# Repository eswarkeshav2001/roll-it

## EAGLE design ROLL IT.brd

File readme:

Guys,Here i have add all the necessary files
PCB credits:Manikandan paramasivam

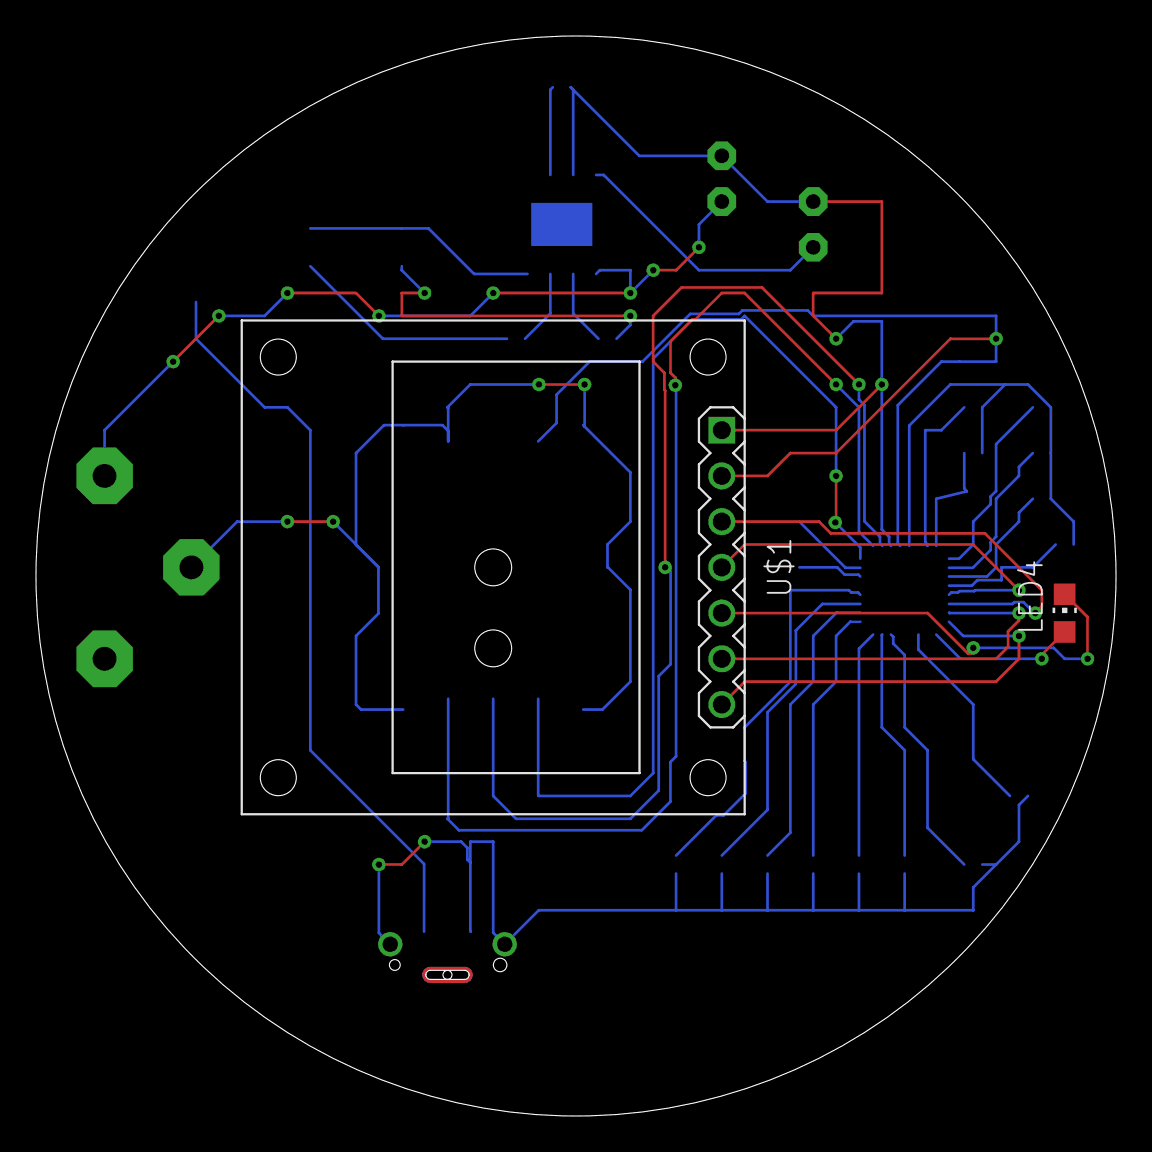
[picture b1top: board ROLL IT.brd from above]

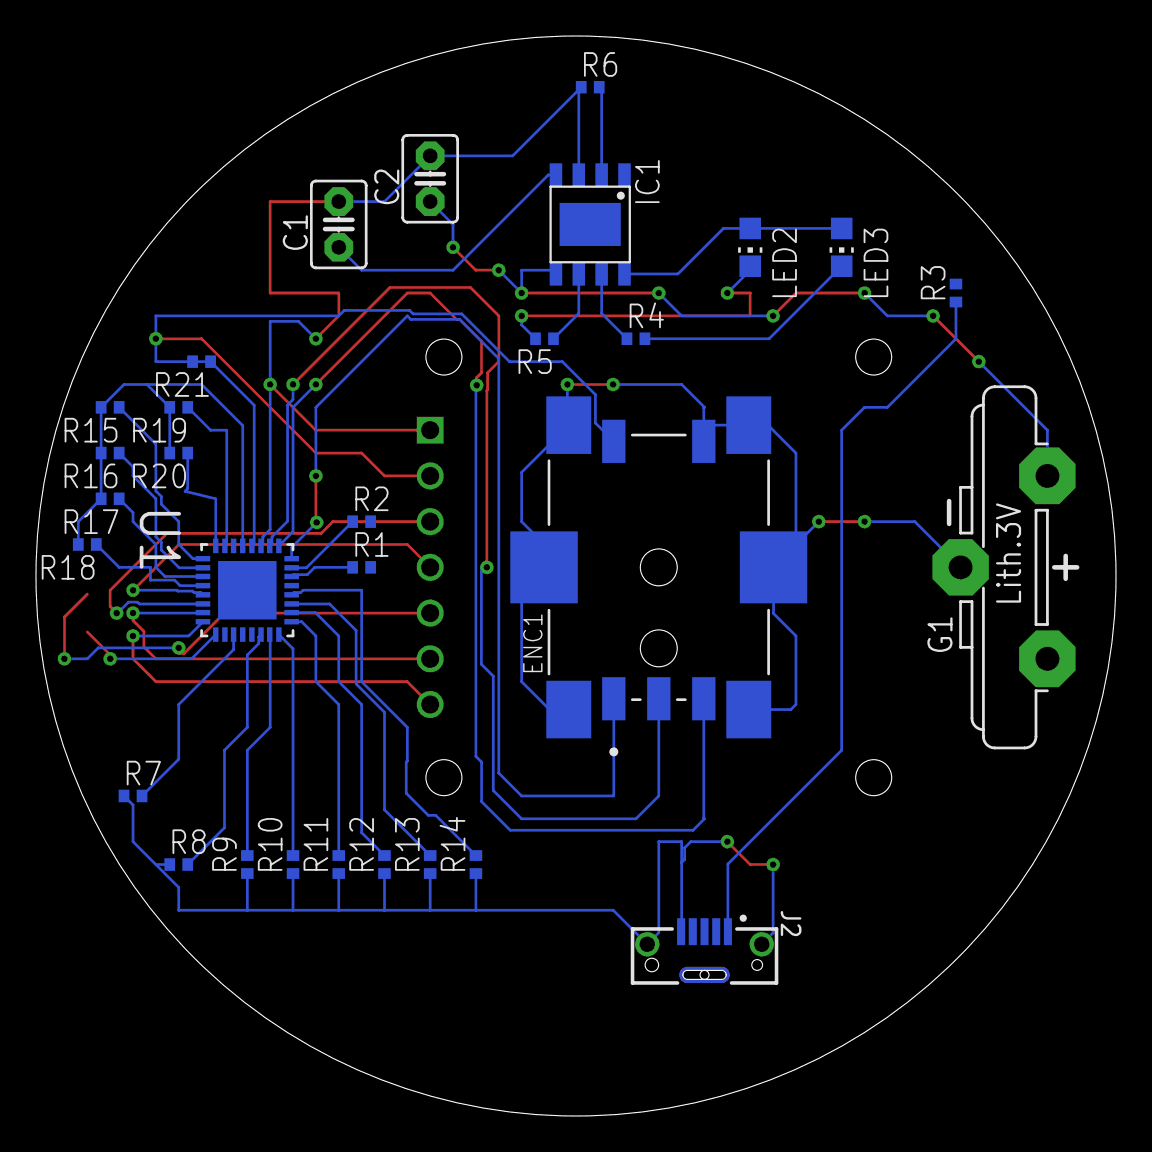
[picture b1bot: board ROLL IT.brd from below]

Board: 2 copper layers, 60.0 x 60.0 mm, 32 parts (30 on the bottom side), 35 nets.

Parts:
C1, C2: 10uF; C2.5-3
ENC1: BOURNS_PEC11S-9220K-S0015BOURNS_PEC11S-9220K-S001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; BOURNS_PEC11S-9220K-S0015_0
G1: CR2032V
IC1: TP4056; SOP-8
J2: USB3160-XX-XXXX-X-X_REVA; GCT_USB3160-XX-XXXX-X-X_REVA
LED2, LED3, LED4: CHIP-LED0805
R1, R2, R4, R5: 1k; R0402
R3: 0.4; R0402
R6: 10k; R0402
R7, R8, R9, R10, R11, R12, R13, R14, R15, R16, R17, R18, R19, R20: 100R; R0402
R21: 10K; R0402
U1: ATMEGA328-MU; QFN50P500X500X100-33N
U$1: DISPLAY-OLED-128X64

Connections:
3V3: C2.1, G1.+, IC1.5
+3V3: ENC1.D, R21.1, R21.2, U1.4, U1.29, U$1.2
CHANNEL_A: ENC1.A, U1.32
CHANNEL_B: ENC1.B, U1.1
GND: C1.2, C2.2, ENC1.1, ENC1.2, ENC1.3, ENC1.4, ENC1.5, ENC1.6, ENC1.E, G1.-, IC1.1, IC1.3, J2.5, J2.6, J2.7, J2.8, R6.1, R7.1, R8.1, R9.1, R10.1, R11.1, R12.1, R13.1, R14.1, R15.2, R16.2, R17.2, R18.2, R19.2, R20.2, U1.3, U1.5, U1.21, U$1.1
unnamed: R7.2, U1.19
unnamed: R1.1, U1.30
unnamed: R2.1, U1.31
unnamed: C1.1, IC1.4, IC1.8, LED2.A, LED3.A, R3.2
unnamed: IC1.6, R5.1
unnamed: IC1.2, R6.2
unnamed: R8.2, U1.22
unnamed: R9.2, U1.23
unnamed: LED2.C, R5.2
unnamed: LED3.C, R4.2
unnamed: IC1.7, R4.1
unnamed: R10.2, U1.24
unnamed: R11.2, U1.25
unnamed: R12.2, U1.26
unnamed: R13.2, U1.27
unnamed: R14.2, U1.28
unnamed: R15.1, U1.9
unnamed: R16.1, U1.10
unnamed: R17.1, U1.11
unnamed: R18.1, U1.12
unnamed: R19.1, U1.7
unnamed: R20.1, U1.8
unnamed: LED4.A, U1.17
OLED_CLK: U1.14, U$1.3
OLED_CS: U1.16, U$1.7
OLED_DC: U1.15, U$1.6
OLED_MOSI: U1.13, U$1.4
OLED_RESET: LED4.C, U$1.5
SWITCH: ENC1.C, U1.2
VCC: J2.1, R3.1

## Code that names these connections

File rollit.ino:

#include <Wire.h>
#include <Adafruit_GFX.h>
#include <Adafruit_SSD1306.h>

int pin1 = 2;
int pin2 = 3;
int pin3 = 5;
int AnalogPin=A5;

int Nticks = 0; 
int State;
int LastState; 
int counter=0; 
int counter_state;
int prestate=0;

const float pi = 3.14;
const float R = 3.45;
float batAnalog=0;
int   bat=0;
const int N = 40;

float distance = 0;
float distance1=0;
float distance2=0;
String thisString;

#define SCREEN_WIDTH 128 
#define SCREEN_HEIGHT 64 
#define OLED_MOSI   9
#define OLED_CLK   10
#define OLED_DC    11
#define OLED_CS    12
#define OLED_RESET 13
Adafruit_SSD1306 display(SCREEN_WIDTH, SCREEN_HEIGHT,
  OLED_MOSI, OLED_CLK, OLED_DC, OLED_RESET, OLED_CS);
  

  
void setup() {
  Serial.begin(9600);
 pinMode (pin1 ,INPUT_PULLUP);
  pinMode (pin2 ,INPUT_PULLUP);
  pinMode(pin3,INPUT);
  if(!display.begin(SSD1306_SWITCHCAPVCC, 0x3C)) { // Address 0x3D for 128x64
    Serial.println(F("SSD1306 allocation failed"));
  
  }
  delay(2000);
  display.clearDisplay();
  display.setTextSize(1);
  display.setTextColor(WHITE);
 
   

  
}

void loop() {

     counter_state=digitalRead(pin3);
   
     
     if(counter_state==HIGH && prestate==0)
     {
      if(counter<=3)
      {
        counter++;
        prestate=1;
      }
     }
     else if(counter_state==LOW)
     {
      prestate=0;
     }
     
     if(counter>3)
     {
      counter=0;
     }
     Serial.print("count");
     Serial.println(counter);
     
    State = digitalRead(pin1);
   if (State != LastState){     
     if (digitalRead(pin2) != State) { 
       Nticks ++;
     } 
     
     else {
       Nticks --;
     }
   } 

  distance = ((2*pi*R)/N) * Nticks ;
  distance=distance*-1;
  thisString = String(distance);
   
  
  LastState = State;

  if (counter==0)
  {
  display.setCursor(10,10);
  display.print(distance);
  display.print(" Cm");
  display.display();
  Serial.println(distance);
  display.clearDisplay();
  }
  if (counter==1)
  {
  distance1=(distance/100);
  display.setCursor(10,10);
  display.print(distance1);
  display.print(" M");
  display.display();
  Serial.println(distance);
  display.clearDisplay();
    
  }
  if (counter==2)
  {
  distance2=(distance*10);
  display.setCursor(10,10);
  display.print(distance2);
  display.print(" mm");
  display.display();
  Serial.println(distance);
  display.clearDisplay();
  }
 if(counter==3)
  {
    batAnalog=analogRead(A5);
    {
      batAnalog=(batAnalog*5.0)/1024.0;
      delay(500);
      bat=((batAnalog/5.0)*100);
      display.setCursor(10,10);
      display.print("Battery aval ");
      display.print(bat);
      display.print("%");
      display.display();
      Serial.println(bat);
      display.clearDisplay();
      
    }
  }
}
  
    
  
  

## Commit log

2021-02-05 Create roll it Arduino code

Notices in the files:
parts and their libraries:
128x64 OLED: Released under the Creative Commons Attribution 4.0 International License: http://creativecommons.org/licenses/by/4.0
